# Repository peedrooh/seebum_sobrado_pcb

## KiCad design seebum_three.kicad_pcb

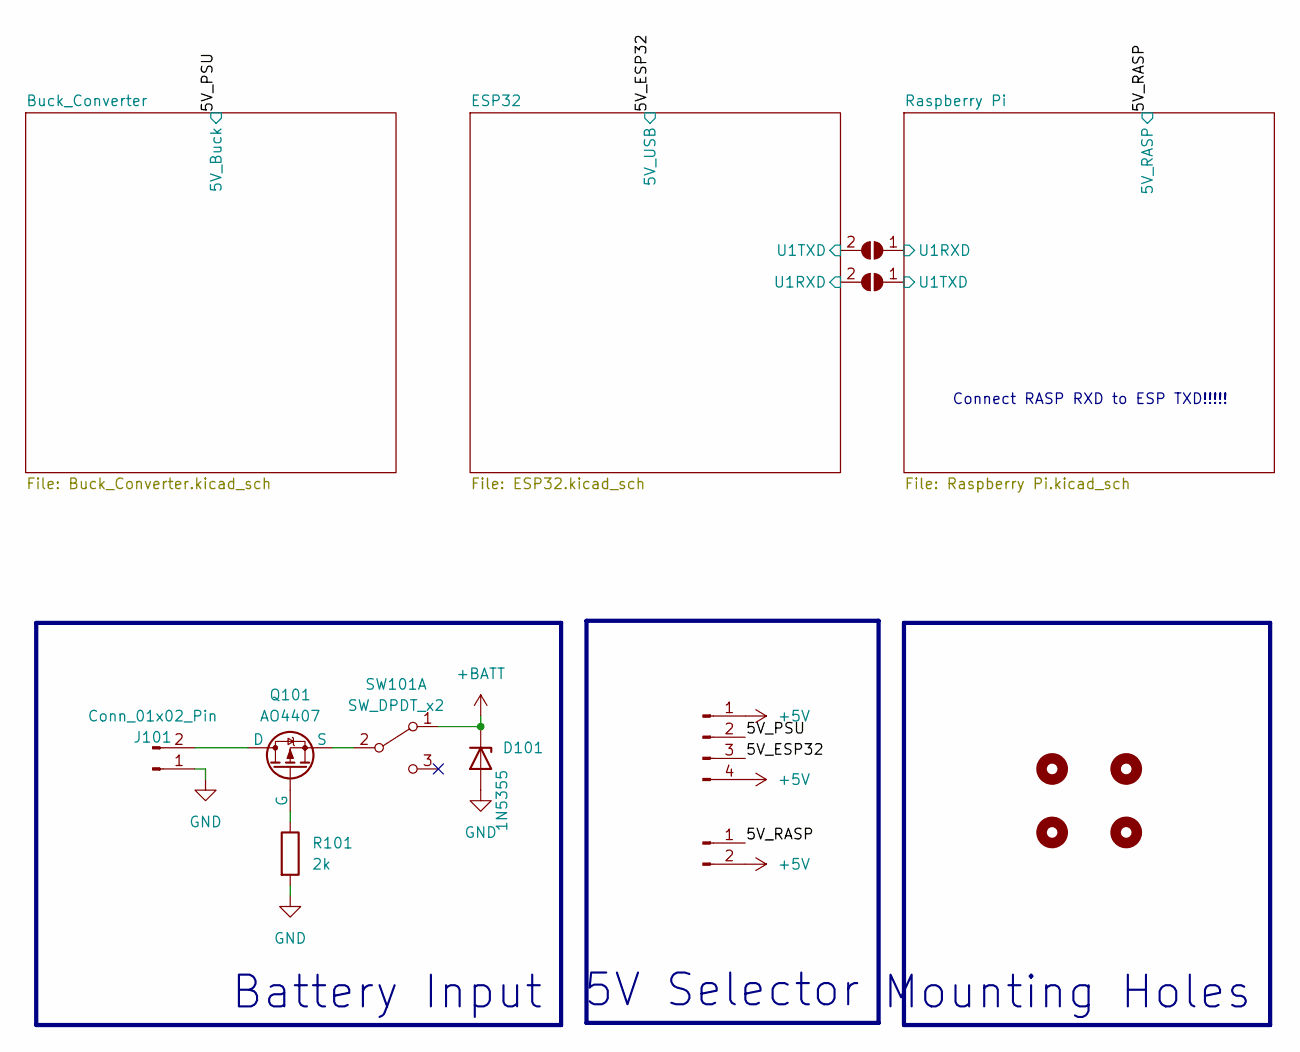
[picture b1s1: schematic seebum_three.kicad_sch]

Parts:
D101: 1N5355; D_DO-201_P3.81mm_Vertical_AnodeUp
H101, H102, H103, H104: MountingHole; M2.5M3
J101: Conn_01x02_Pin; AMASS_XT30UPB-M_1x02_P5.0mm_Vertical
J102: Conn_01x04_Pin; PinHeader_2x02_P2.54mm_Vertical
J103: Conn_01x02_Pin; PinHeader_1x02_P2.54mm_Vertical
JP103, JP104: SolderJumper_2_Open; SolderJumper-2_P1.3mm_Bridged_RoundedPad1.0x1.5mm
Q101: AO4407; SOP-8_3.76x4.96mm_P1.27mm; LCSC C469397
R101: 2k; R_0805_2012Metric; LCSC C17604
SW101: SW_DPDT_x2; 5Amp_Switch; LCSC C2884744

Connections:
+5V: J102.1, J102.4, J103.2; also elsewhere on the board
+BATT: D101.1 (K), SW101.1 (A); also elsewhere on the board
/5V_ESP32: J102.3; also elsewhere on the board
/5V_PSU: J102.2; also elsewhere on the board
/5V_RASP: J103.1; also elsewhere on the board
/ESP32/GPIO17: JP104.2 (B); also elsewhere on the board
/ESP32/GPIO18: JP103.2 (B); also elsewhere on the board
/Raspberry Pi/RASP_RX: JP103.1 (A); also elsewhere on the board
/Raspberry Pi/RASP_TX: JP104.1 (A); also elsewhere on the board
GND: D101.2 (A), J101.1, R101.2; also elsewhere on the board
unnamed: J101.2, Q101.1 (D)
unnamed: Q101.2 (G), R101.1
unnamed: Q101.3 (S), SW101.2 (B)

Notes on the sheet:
Battery Input
Connect RASP RXD to ESP TXD!!!!!
5V Selector
Mounting Holes

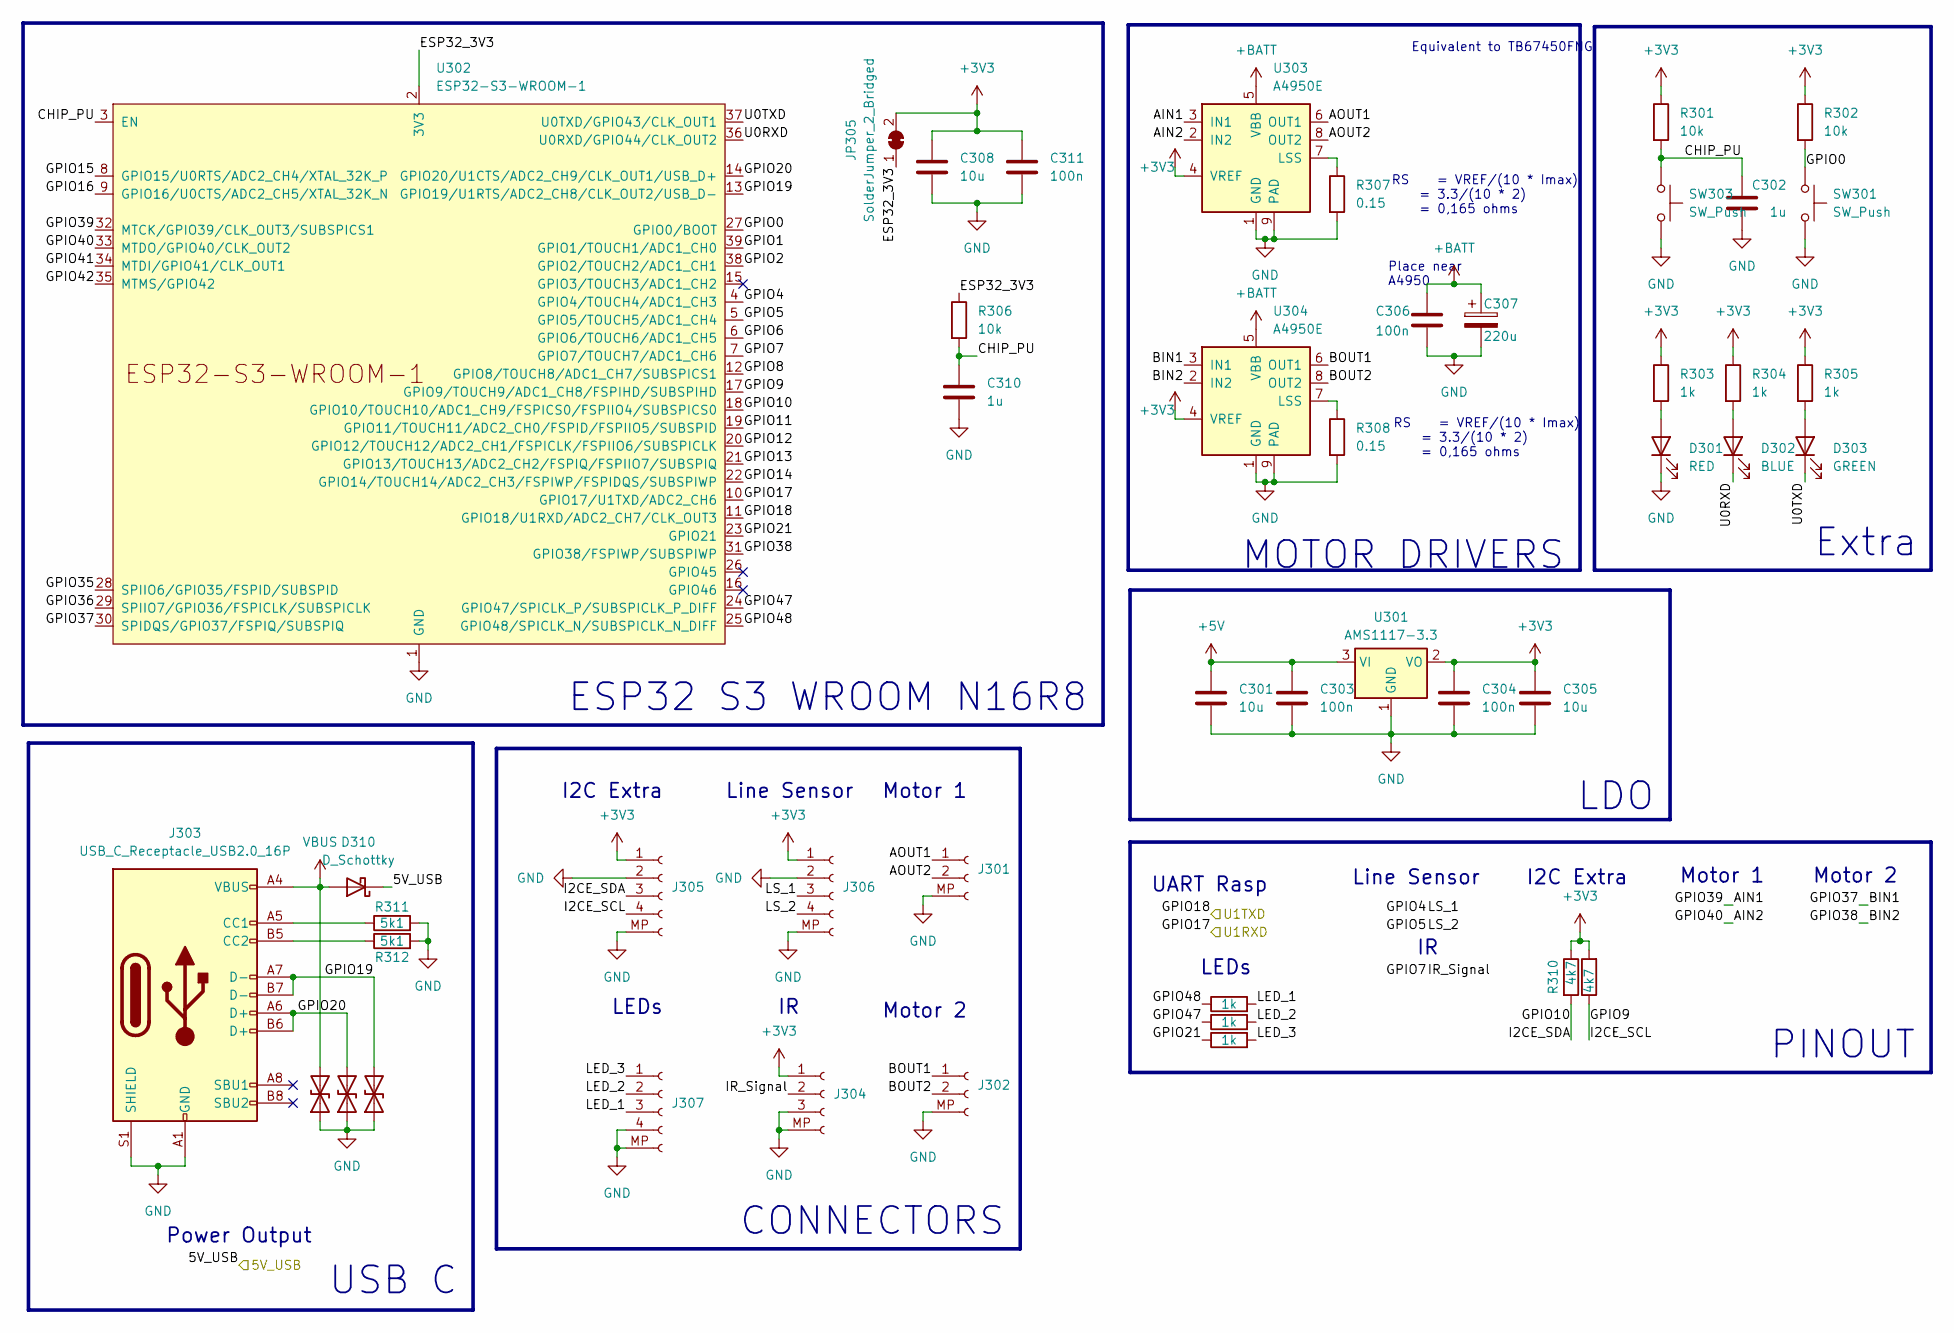
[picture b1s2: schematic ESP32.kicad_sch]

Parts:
C301, C305, C308: 10u; C_0805_2012Metric_Pad1.18x1.45mm_HandSolder
C302, C310: 1u; C_0805_2012Metric_Pad1.18x1.45mm_HandSolder
C303, C304, C306, C311: 100n; C_0805_2012Metric_Pad1.18x1.45mm_HandSolder
C307: 220u; CP_Radial_D10.0mm_P5.00mm
D301: RED; LED_0805_2012Metric
D302: BLUE; LED_0805_2012Metric; LCSC C205441
D303: GREEN; LED_0805_2012Metric; LCSC C84260
D308, D309, D311: D_TVS; D_SOD-523; LCSC C383211
D310: D_Schottky; D_SOD-323; LCSC C2891705
J301, J302: Conn_01x02_Socket; JST_PH_B2B-PH-SM4-TB_1x02-1MP_P2.00mm_Vertical; LCSC C160352
J303: USB_C_Receptacle_USB2.0_16P; USB_C_Receptacle_G-Switch_GT-USB-7010ASV; LCSC C2765186
J304: Conn_01x03_Socket; JST_PH_B3B-PH-SM4-TB_1x03-1MP_P2.00mm_Vertical; LCSC C160353
J305, J306, J307: Conn_01x04_Socket; JST_PH_B4B-PH-SM4-TB_1x04-1MP_P2.00mm_Vertical
JP305: SolderJumper_2_Bridged; SolderJumper-2_P1.3mm_Bridged_RoundedPad1.0x1.5mm
R301, R302, R306: 10k; R_0805_2012Metric_Pad1.20x1.40mm_HandSolder
R303, R304, R305, R313, R314, R315: 1k; R_0805_2012Metric_Pad1.20x1.40mm_HandSolder
R307, R308: 0.15; R_2512_6332Metric_Pad1.40x3.35mm_HandSolder
R309, R310: 4k7; R_0805_2012Metric; LCSC C17673
R311, R312: 5k1; R_0603_1608Metric_Pad0.98x0.95mm_HandSolder
SW301, SW303: SW_Push; SW_SPST_B3U-1000P
U301: AMS1117-3.3; SOT-223-3_TabPin2; LCSC C347222
U302: ESP32-S3-WROOM-1; LCSC C2913205
U303, U304: A4950E; SOIC-8-1EP_3.9x4.9mm_P1.27mm_EP2.41x3.3mm

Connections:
+3V3: C304.1, C305.1, C308.1, C311.1, J304.1, J305.1, J306.1, JP305.2 (B), R301.1, R302.1, R303.1, R304.1, R305.1, R309.2, R310.1, U301.2 (VO), U303.4 (VREF), U304.4 (VREF)
+5V: C301.1, C303.1, U301.3 (VI); also elsewhere on the board
+BATT: C306.1, C307.1, U303.5 (VBB), U304.5 (VBB); also elsewhere on the board
/5V_ESP32: D310.1 (K); also elsewhere on the board
/ESP32/AIN1: U302.32 (MTCK/GPIO39/CLK_OUT3/SUBSPICS1), U303.3 (IN1)
/ESP32/AIN2: U302.33 (MTDO/GPIO40/CLK_OUT2), U303.2 (IN2)
/ESP32/AOUT1: J301.1, U303.6 (OUT1)
/ESP32/AOUT2: J301.2, U303.8 (OUT2)
/ESP32/BIN1: U302.30 (SPIDQS/GPIO37/FSPIQ/SUBSPIQ), U304.3 (IN1)
/ESP32/BIN2: U302.31 (GPIO38/FSPIWP/SUBSPIWP), U304.2 (IN2)
/ESP32/BOUT1: J302.1, U304.6 (OUT1)
/ESP32/BOUT2: J302.2, U304.8 (OUT2)
/ESP32/CHIP_PU: C302.1, C310.1, R301.2, R306.2, SW303.1, U302.3 (EN)
/ESP32/ESP32_3V3: JP305.1 (A), R306.1, U302.2 (3V3)
/ESP32/GPIO0: R302.2, SW301.1, U302.27 (GPIO0/BOOT)
/ESP32/GPIO1: U302.39 (GPIO1/TOUCH1/ADC1_CH0)
/ESP32/GPIO2: U302.38 (GPIO2/TOUCH2/ADC1_CH1)
/ESP32/GPIO4: J306.3, U302.4 (GPIO4/TOUCH4/ADC1_CH3)
/ESP32/GPIO5: J306.4, U302.5 (GPIO5/TOUCH5/ADC1_CH4)
/ESP32/GPIO6: U302.6 (GPIO6/TOUCH6/ADC1_CH5)
/ESP32/GPIO7: J304.2, U302.7 (GPIO7/TOUCH7/ADC1_CH6)
/ESP32/GPIO8: U302.12 (GPIO8/TOUCH8/ADC1_CH7/SUBSPICS1)
/ESP32/GPIO9: J305.4, R309.1, U302.17 (GPIO9/TOUCH9/ADC1_CH8/FSPIHD/SUBSPIHD)
/ESP32/GPIO10: J305.3, R310.2, U302.18 (GPIO10/TOUCH10/ADC1_CH9/FSPICS0/FSPIIO4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)
/ESP32/GPIO11: U302.19 (GPIO11/TOUCH11/ADC2_CH0/FSPID/FSPIIO5/S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)
/ESP32/GPIO12: U302.20 (GPIO12/TOUCH12/ADC2_CH1/FSPICLK/FSPIIO6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)
/ESP32/GPIO13: U302.21 (GPIO13/TOUCH13/ADC2_CH2/FSPIQ/FSPIIO7/S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)
/ESP32/GPIO14: U302.22 (GPIO14/TOUCH14/ADC2_CH3/FSPIWP/FSPIDQS/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)
/ESP32/GPIO15: U302.8 (GPIO15/U0RTS/ADC2_CH4/XTAL_32K_P)
/ESP32/GPIO16: U302.9 (GPIO16/U0CTS/ADC2_CH5/XTAL_32K_N)
/ESP32/GPIO17: U302.10 (GPIO17/U1TXD/ADC2_CH6); also elsewhere on the board
/ESP32/GPIO18: U302.11 (GPIO18/U1RXD/ADC2_CH7/CLK_OUT3); also elsewhere on the board
/ESP32/GPIO19: D311.2 (A2), J303.A7 (D-), J303.B7 (D-), U302.13 (GPIO19/U1RTS/ADC2_CH8/CLK_OUT2/USB_D-)
/ESP32/GPIO20: D309.2 (A2), J303.A6 (D+), J303.B6 (D+), U302.14 (GPIO20/U1CTS/ADC2_CH9/CLK_OUT1/USB_D+)
/ESP32/GPIO21: R315.1, U302.23 (GPIO21)
/ESP32/GPIO35: U302.28 (SPIIO6/GPIO35/FSPID/SUBSPID)
/ESP32/GPIO36: U302.29 (SPIIO7/GPIO36/FSPICLK/SUBSPICLK)
/ESP32/GPIO41: U302.34 (MTDI/GPIO41/CLK_OUT1)
/ESP32/GPIO42: U302.35 (MTMS/GPIO42)
/ESP32/GPIO47: R314.1, U302.24 (GPIO47/SPICLK_P/SUBSPICLK_P_DIFF)
/ESP32/GPIO48: R313.1, U302.25 (GPIO48/SPICLK_N/SUBSPICLK_N_DIFF)
/ESP32/LED_1: J307.3, R313.2
/ESP32/LED_2: J307.2, R314.2
/ESP32/LED_3: J307.1, R315.2
/ESP32/U0RXD: D302.1 (K), U302.36 (U0RXD/GPIO44/CLK_OUT2)
/ESP32/U0TXD: D303.1 (K), U302.37 (U0TXD/GPIO43/CLK_OUT1)
GND: C301.2, C302.2, C303.2, C304.2, C305.2, C306.2, C307.2, C308.2, C310.2, C311.2, D301.1 (K), D308.1 (A1), D309.1 (A1), D311.1 (A1), J301.MP (Pin_3), J302.MP (Pin_3), J303.A1 (GND), J303.A12 (GND), J303.B1 (GND), J303.B12 (GND), J303.S1 (SHIELD), J304.3, J304.MP (Pin_4), J305.2, J305.MP (Pin_5), J306.2, J306.MP (Pin_5), J307.4, J307.MP (Pin_5), R307.2, R308.2, R311.2, R312.2, SW301.2, SW303.2, U301.1 (GND), U302.1 (GND), U302.40 (GND), U302.41 (GND), U303.1 (GND), U303.9 (PAD), U304.1 (GND), U304.9 (PAD); also elsewhere on the board
unnamed: D301.2 (A), R303.2
unnamed: D302.2 (A), R304.2
unnamed: D303.2 (A), R305.2
unnamed: J303.A5 (CC1), R311.1
unnamed: J303.B5 (CC2), R312.1
unnamed: R307.1, U303.7 (LSS)
unnamed: R308.1, U304.7 (LSS)
VBUS: D308.2 (A2), D310.2 (A), J303.A4 (VBUS), J303.A9 (VBUS), J303.B4 (VBUS), J303.B9 (VBUS)

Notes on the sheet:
PINOUT
RS = VREF/(10 * Imax) = 3.3/(10 * 2) = 0,165 ohms
USB C
Place near A4950
ESP32 S3 WROOM N16R8
Motor 2
Line Sensor
LEDs
I2C Extra
Motor 1
Power Output
MOTOR DRIVERS
CONNECTORS
Equivalent to TB67450FNG
Extra
LDO
UART Rasp

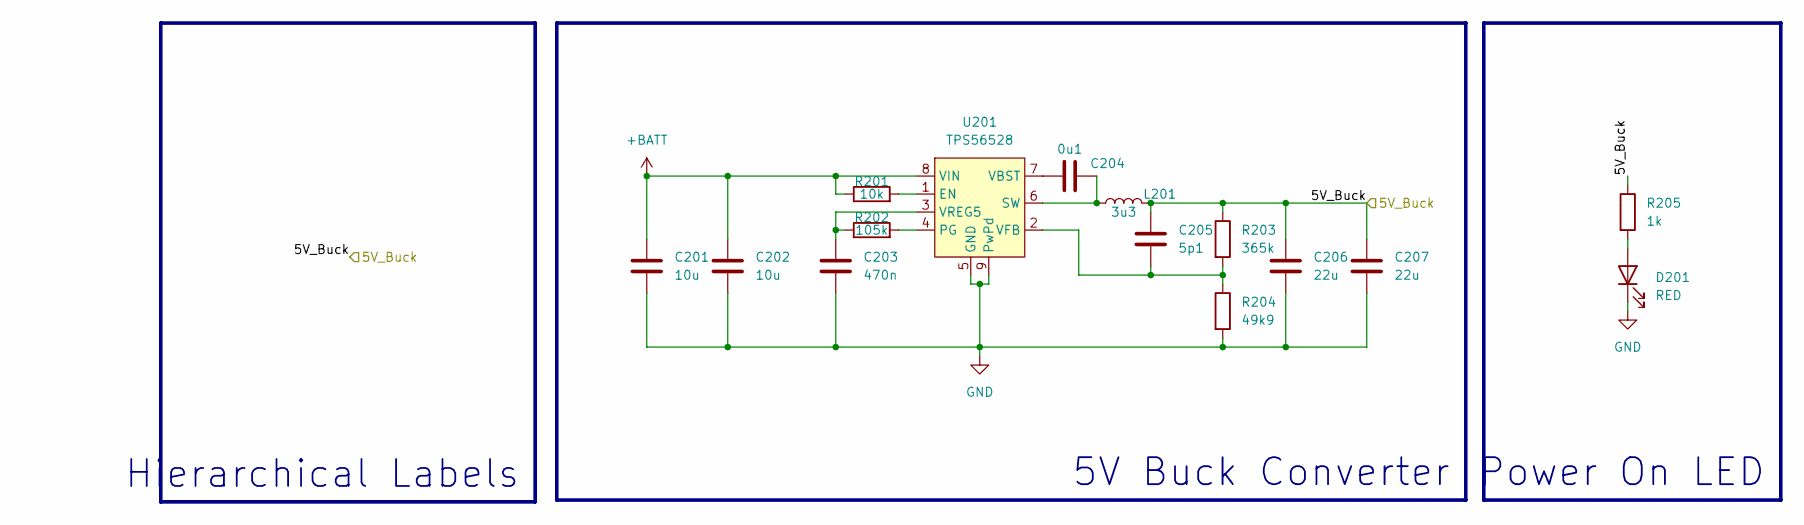
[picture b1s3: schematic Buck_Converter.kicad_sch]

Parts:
C201: 10u; C_1210_3225Metric_Pad1.33x2.70mm_HandSolder; LCSC C2918502
C202: 10u; C_1210_3225Metric_Pad1.33x2.70mm_HandSolder
C203: 470n; C_0805_2012Metric_Pad1.18x1.45mm_HandSolder
C204: 0u1; C_0805_2012Metric_Pad1.18x1.45mm_HandSolder
C205: 5p1; C_0805_2012Metric_Pad1.18x1.45mm_HandSolder
C206, C207: 22u; C_0805_2012Metric_Pad1.18x1.45mm_HandSolder
D201: RED; LED_0805_2012Metric
L201: 3u3; L_Bourns_SRP1050WA; LCSC C497894
R201: 10k; R_0805_2012Metric_Pad1.20x1.40mm_HandSolder
R202: 105k; R_0805_2012Metric_Pad1.20x1.40mm_HandSolder; LCSC C3000727
R203: 365k; R_0805_2012Metric_Pad1.20x1.40mm_HandSolder; LCSC C2999471
R204: 49k9; R_0805_2012Metric_Pad1.20x1.40mm_HandSolder; LCSC C17719
R205: 1k; R_0805_2012Metric_Pad1.20x1.40mm_HandSolder
U201: TPS56528; Texas_HSOP-8-1EP_3.9x4.9mm_P1.27mm_ThermalVias; LCSC C138716

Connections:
+BATT: C201.1, C202.1, R201.1, U201.8 (VIN); also elsewhere on the board
/5V_PSU: C205.1, C206.1, C207.1, L201.2, R203.1, R205.1; also elsewhere on the board
GND: C201.2, C202.2, C203.2, C206.2, C207.2, D201.1 (K), R204.2, U201.5 (GND), U201.9 (PwPd); also elsewhere on the board
unnamed: D201.2 (A), R205.2
unnamed: R201.2, U201.1 (EN)
unnamed: R202.2, U201.4 (PG)
unnamed: C204.2, L201.1, U201.6 (SW)
unnamed: C204.1, U201.7 (VBST)
unnamed: C205.2, R203.2, R204.1, U201.2 (VFB)
unnamed: C203.1, R202.1, U201.3 (VREG5)

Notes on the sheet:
Power On LED
Hierarchical Labels
5V Buck Converter

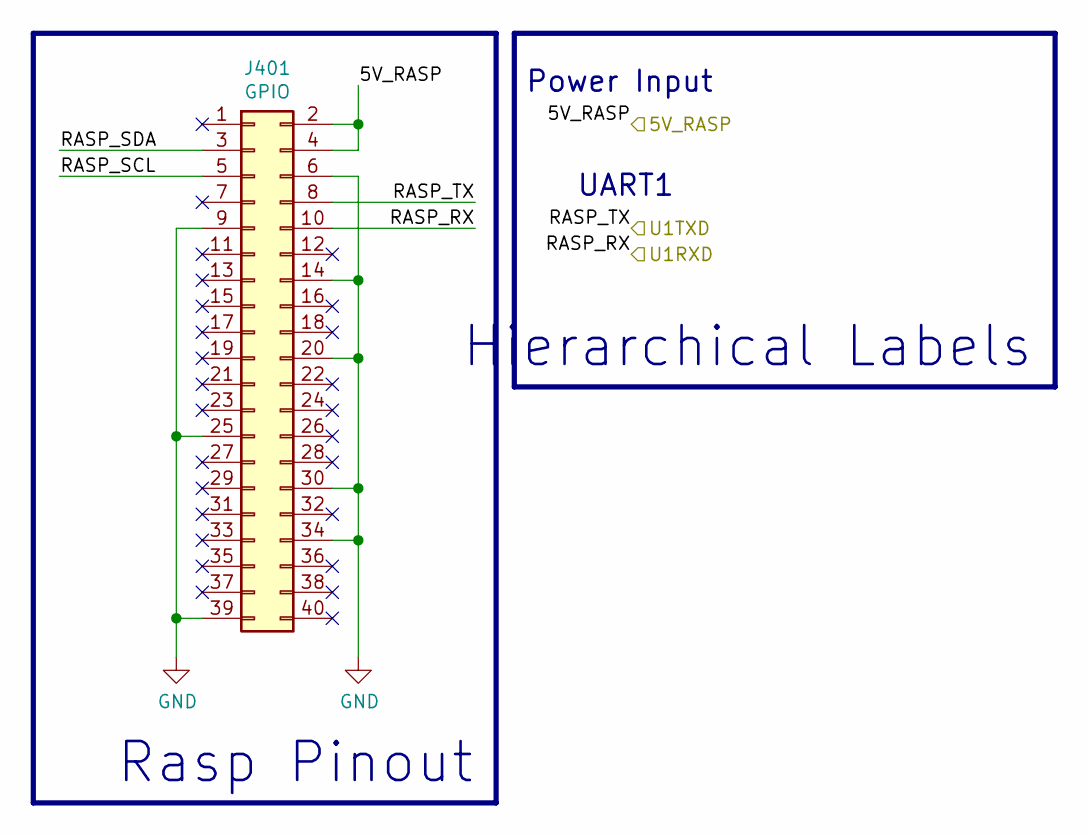
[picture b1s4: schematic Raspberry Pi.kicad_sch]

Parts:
J401: GPIO; PinSocket_2x20_P2.54mm_Vertical

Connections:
/5V_RASP: J401.2, J401.4; also elsewhere on the board
/Raspberry Pi/RASP_RX: J401.10; also elsewhere on the board
/Raspberry Pi/RASP_SCL: J401.5
/Raspberry Pi/RASP_SDA: J401.3
/Raspberry Pi/RASP_TX: J401.8; also elsewhere on the board
GND: J401.6, J401.9, J401.14, J401.20, J401.25, J401.30, J401.34, J401.39; also elsewhere on the board

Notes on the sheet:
Power Input
Rasp Pinout
Hierarchical Labels
UART1

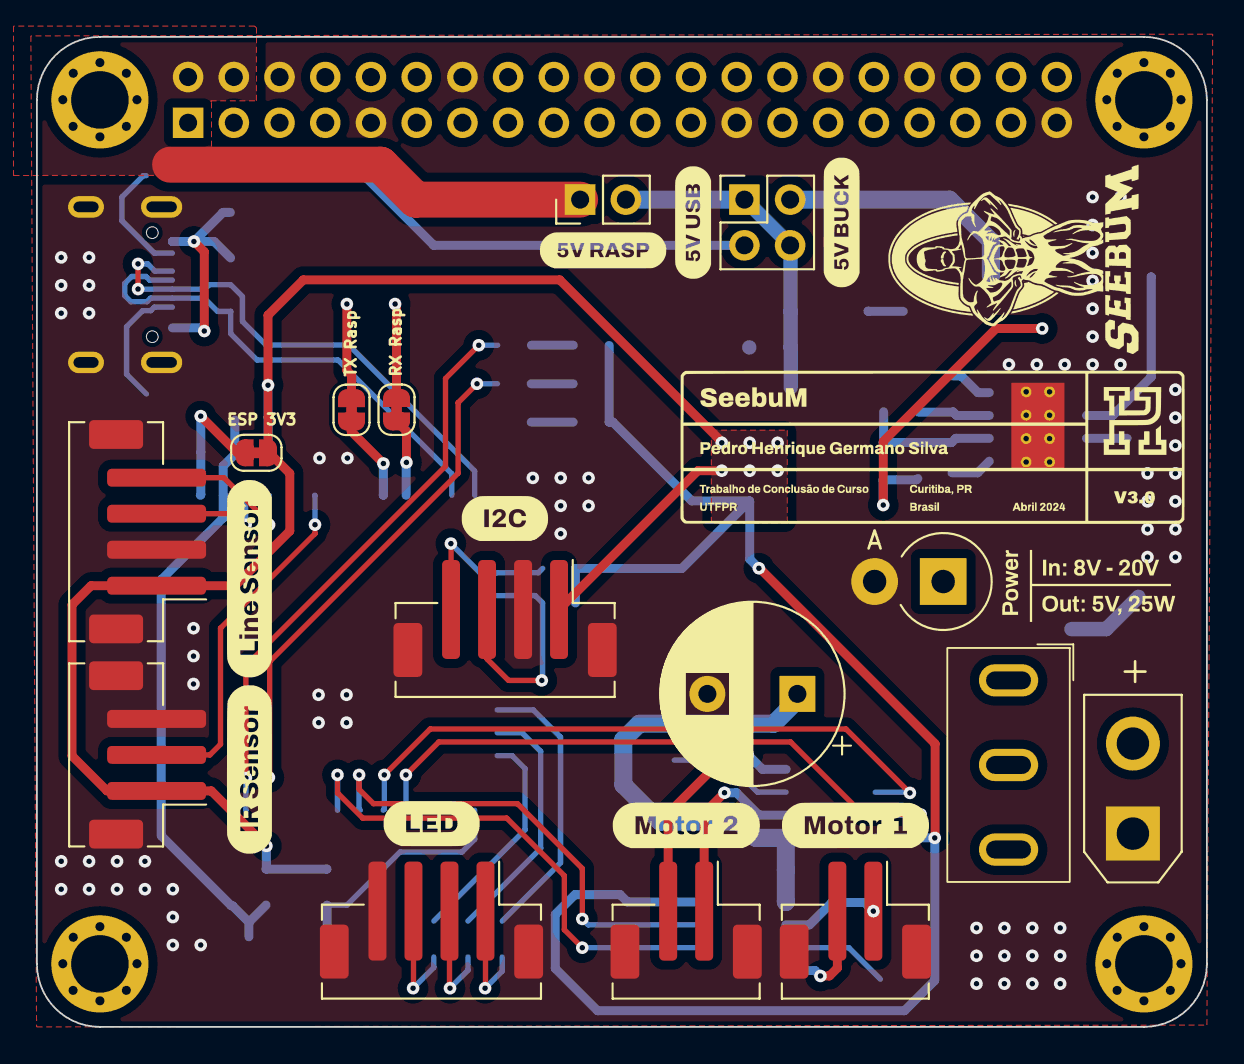
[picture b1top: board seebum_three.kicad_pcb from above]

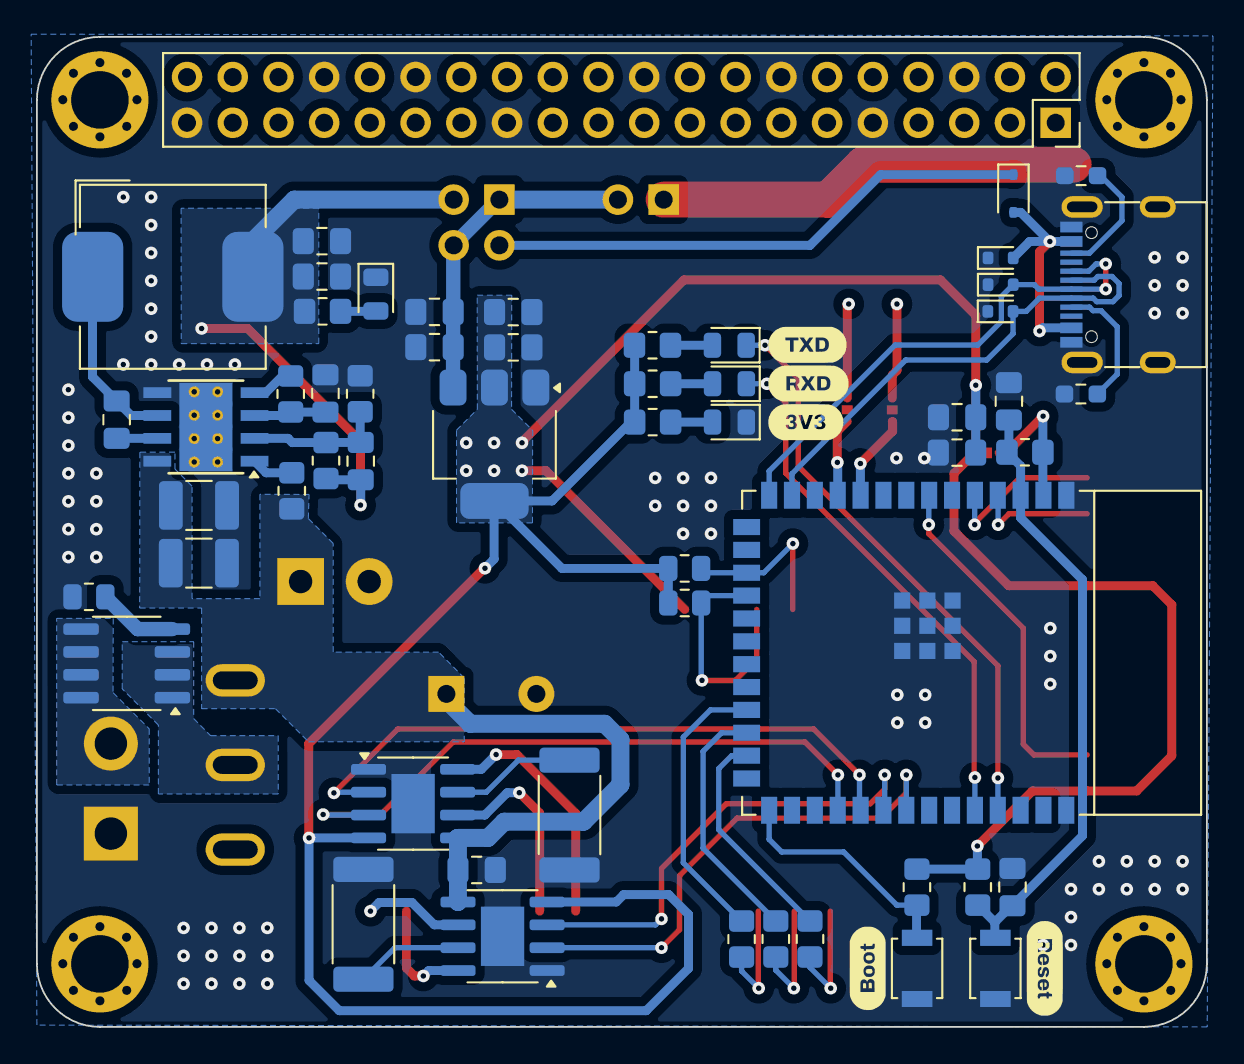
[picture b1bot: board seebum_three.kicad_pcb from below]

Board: 4 copper layers, 65.0 x 55.0 mm, 75 parts (56 on the bottom side), 55 nets.

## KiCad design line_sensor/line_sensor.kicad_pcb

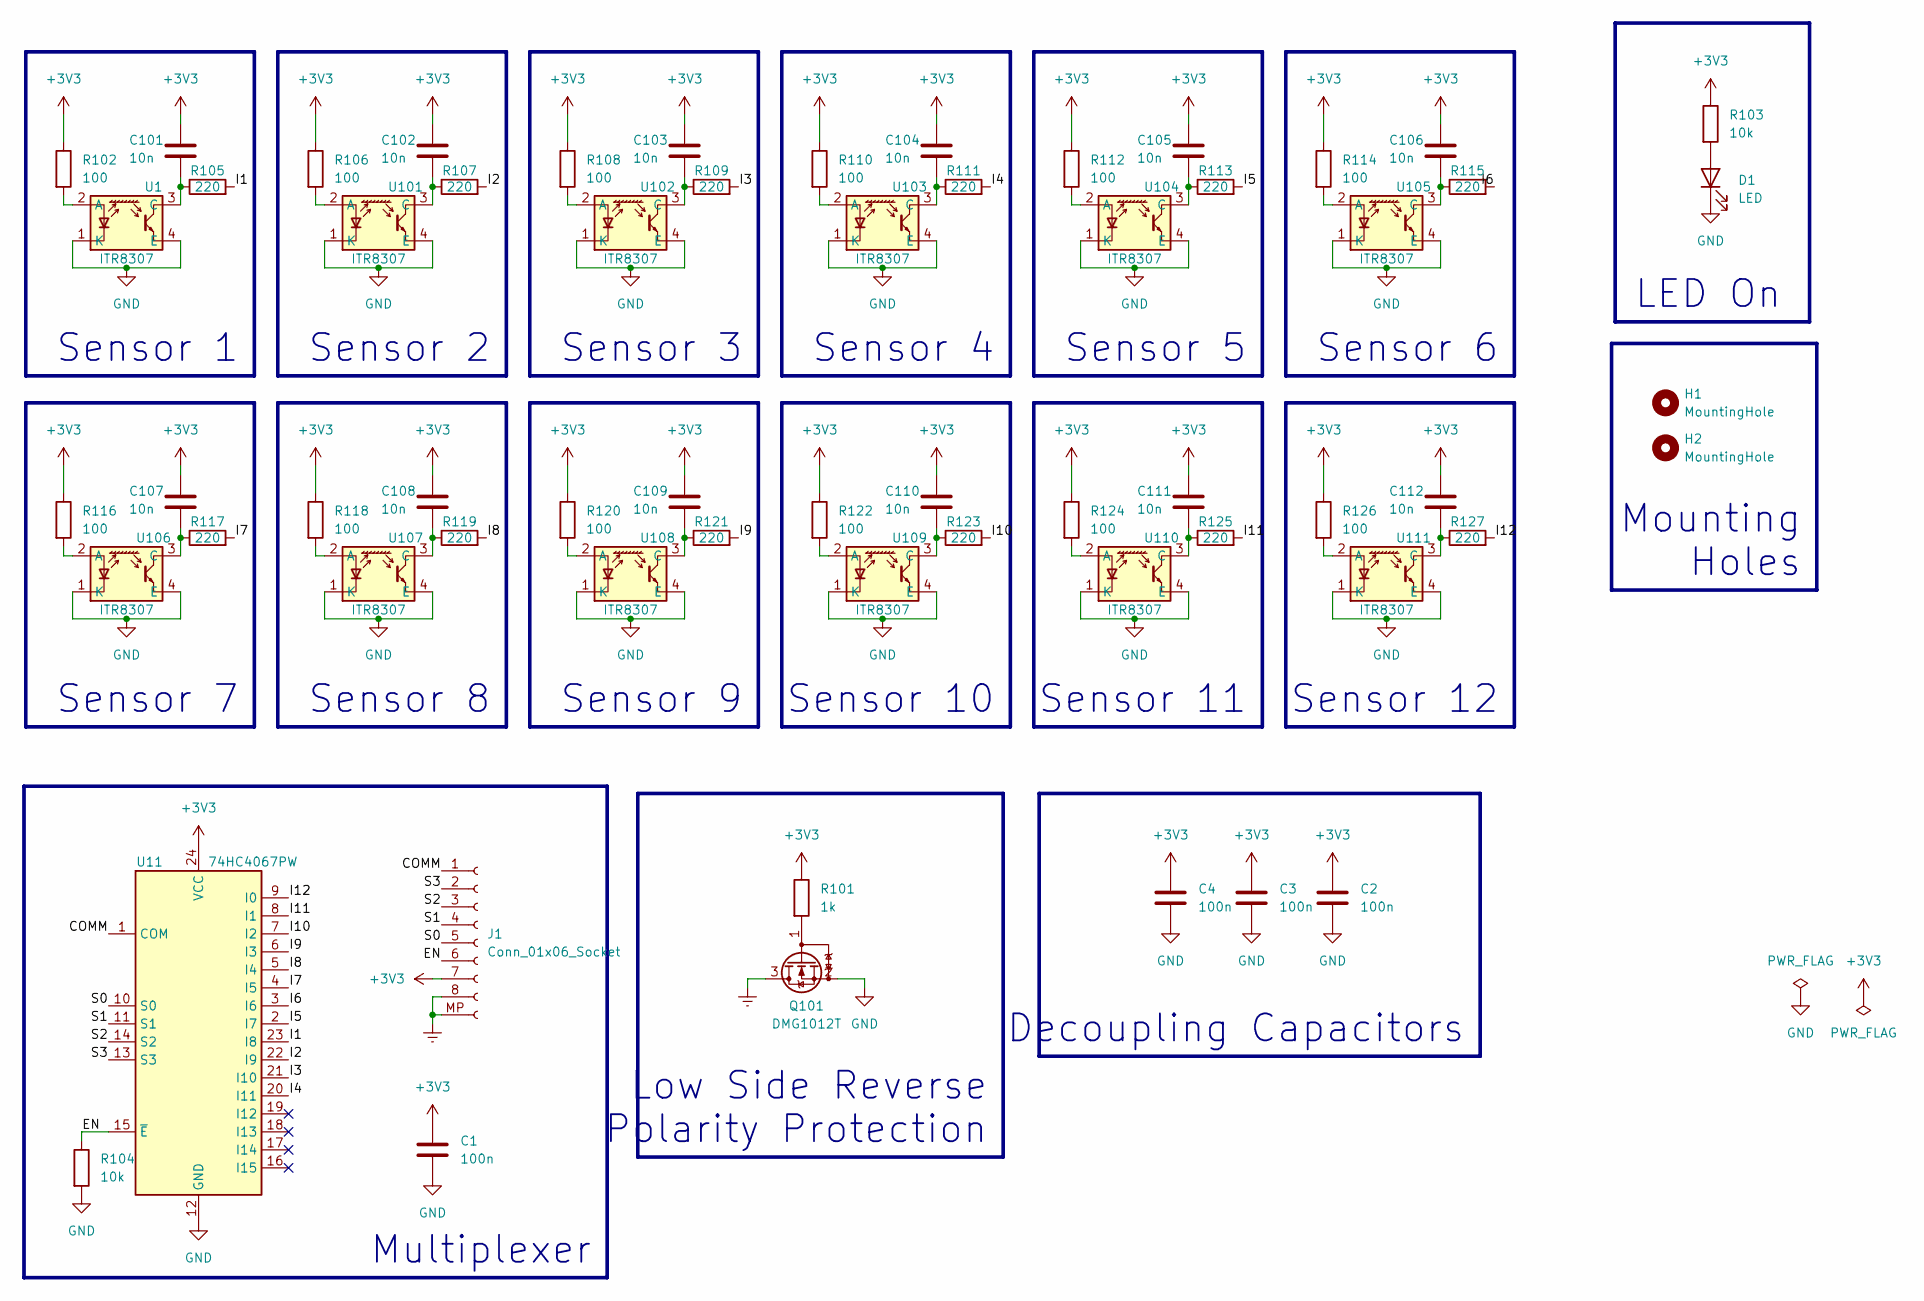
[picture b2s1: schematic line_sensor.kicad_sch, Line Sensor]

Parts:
C1, C2, C3, C4: 100n; C_0805_2012Metric_Pad1.18x1.45mm_HandSolder; LCSC C38141
C101, C102, C103, C104, C105, C106, C107, C108, C109, C110, C111, C112: 10n; C_0805_2012Metric_Pad1.18x1.45mm_HandSolder
D1: LED; LED_0805_2012Metric; LCSC C391863
H1, H2: MountingHole; MountingHole_3.2mm_M3_Pad_Via
J1: Conn_01x06_Socket; JST_PH_B8B-PH-SM4-TB_1x08-1MP_P2.00mm_Vertical
Q101: DMG1012T; SOT-523; LCSC C20512
R101: 1k; R_0805_2012Metric; LCSC C17513
R102, R106, R108, R110, R112, R114, R116, R118, R120, R122, R124, R126: 100; R_0805_2012Metric
R103, R104: 10k; R_0805_2012Metric
R105, R107, R109, R111, R113, R115, R117, R119, R121, R123, R125, R127: 220; R_0805_2012Metric
U1, U101, U102, U103, U104, U105, U106, U107, U108, U109, U110, U111: ITR8307; ITR8307_S18_TR8_B; LCSC C115037
U11: 74HC4067PW; TSSOP-24_4.4x7.8mm_P0.65mm; LCSC C179326

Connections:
+3V3: C1.1, C2.1, C3.1, C4.1, C101.1, C102.1, C103.1, C104.1, C105.1, C106.1, C107.1, C108.1, C109.1, C110.1, C111.1, C112.1, J1.7, R101.1, R102.1, R103.1, R106.1, R108.1, R110.1, R112.1, R114.1, R116.1, R118.1, R120.1, R122.1, R124.1, R126.1, U11.24 (VCC)
/COMM: J1.1, U11.1 (COM)
/EN: J1.6, R104.1, U11.15 (~E)
/I1: R105.2, U11.23 (I8)
/I2: R107.2, U11.22 (I9)
/I3: R109.2, U11.21 (I10)
/I4: R111.2, U11.20 (I11)
/I5: R113.2, U11.2 (I7)
/I6: R115.2, U11.3 (I6)
/I7: R117.2, U11.4 (I5)
/I8: R119.2, U11.5 (I4)
/I9: R121.2, U11.6 (I3)
/I10: R123.2, U11.7 (I2)
/I11: R125.2, U11.8 (I1)
/I12: R127.2, U11.9 (I0)
/S0: J1.5, U11.10 (S0)
/S1: J1.4, U11.11 (S1)
/S2: J1.3, U11.14 (S2)
/S3: J1.2, U11.13 (S3)
Earth: J1.8, J1.MP (Pin_9), Q101.3 (D)
GND: C1.2, C2.2, C3.2, C4.2, D1.1 (K), Q101.2 (S), R104.2, U1.1 (K), U1.4 (E), U11.12 (GND), U101.1 (K), U101.4 (E), U102.1 (K), U102.4 (E), U103.1 (K), U103.4 (E), U104.1 (K), U104.4 (E), U105.1 (K), U105.4 (E), U106.1 (K), U106.4 (E), U107.1 (K), U107.4 (E), U108.1 (K), U108.4 (E), U109.1 (K), U109.4 (E), U110.1 (K), U110.4 (E), U111.1 (K), U111.4 (E)
unnamed: D1.2 (A), R103.2
unnamed: Q101.1 (G), R101.2
unnamed: R102.2, U1.2 (A)
unnamed: C101.2, R105.1, U1.3 (C)
unnamed: R106.2, U101.2 (A)
unnamed: C102.2, R107.1, U101.3 (C)
unnamed: R108.2, U102.2 (A)
unnamed: C103.2, R109.1, U102.3 (C)
unnamed: R110.2, U103.2 (A)
unnamed: C104.2, R111.1, U103.3 (C)
unnamed: R112.2, U104.2 (A)
unnamed: C105.2, R113.1, U104.3 (C)
unnamed: R114.2, U105.2 (A)
unnamed: C106.2, R115.1, U105.3 (C)
unnamed: R116.2, U106.2 (A)
unnamed: C107.2, R117.1, U106.3 (C)
unnamed: R118.2, U107.2 (A)
unnamed: C108.2, R119.1, U107.3 (C)
unnamed: R120.2, U108.2 (A)
unnamed: C109.2, R121.1, U108.3 (C)
unnamed: R122.2, U109.2 (A)
unnamed: C110.2, R123.1, U109.3 (C)
unnamed: R124.2, U110.2 (A)
unnamed: C111.2, R125.1, U110.3 (C)
unnamed: R126.2, U111.2 (A)
unnamed: C112.2, R127.1, U111.3 (C)

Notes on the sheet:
Low Side Reverse Polarity Protection
Sensor 4
Sensor 3
Sensor 12
Sensor 2
Sensor 8
Sensor 1
Sensor 10
Sensor 5
LED On
Sensor 9
Sensor 11
Sensor 6
Mounting Holes
Decoupling Capacitors
Multiplexer
Sensor 7

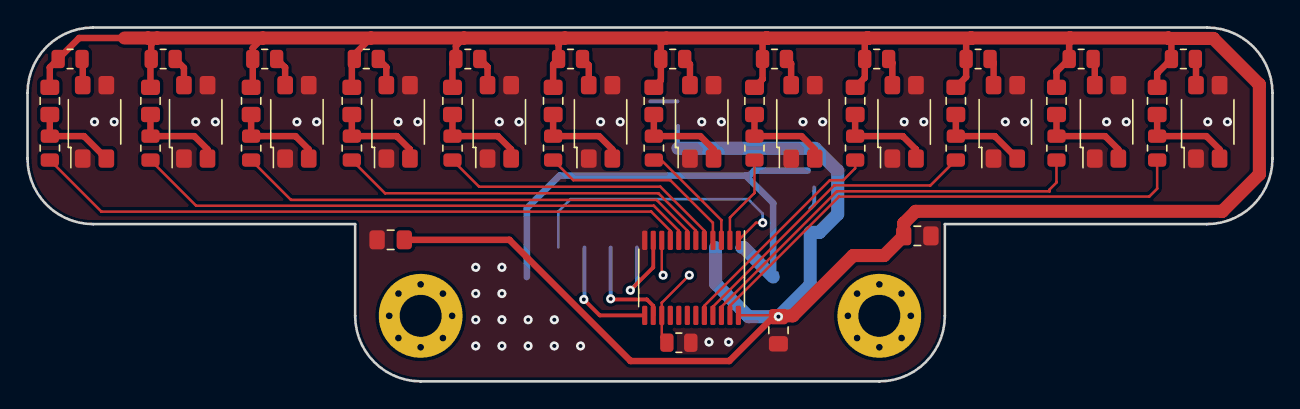
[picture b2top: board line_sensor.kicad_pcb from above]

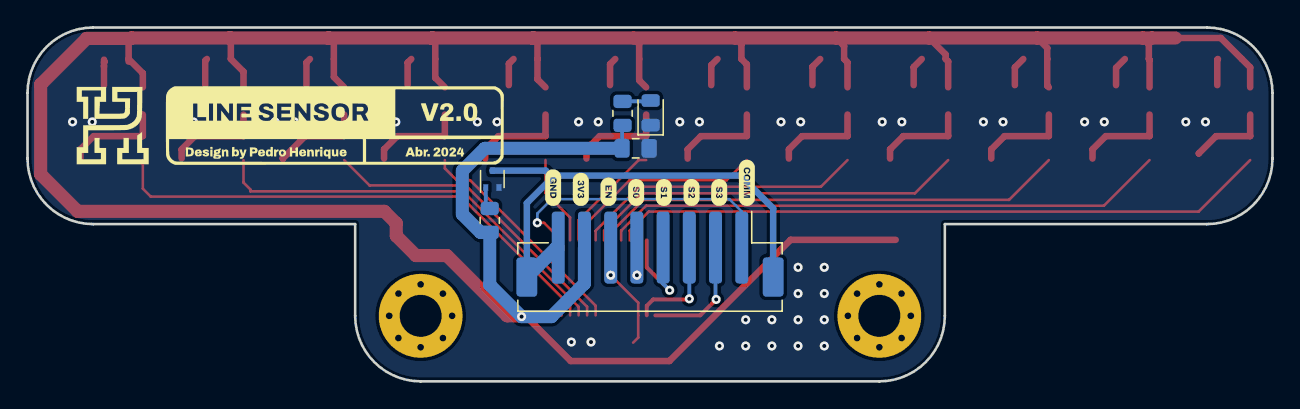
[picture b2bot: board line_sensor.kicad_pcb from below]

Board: 2 copper layers, 95.0 x 27.0 mm, 61 parts (6 on the bottom side), 47 nets.

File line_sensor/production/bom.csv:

Designator,Footprint,Quantity,Value,LCSC Part #
"C1, C2, C3, C4",0805,4,100n,C38141
"C101, C102, C103, C104, C105, C106, C107, C108, C109, C110, C111, C112",0805,12,10n,
D1,0805,1,LED,C391863
"H1, H2",MountingHole_3.2mm_M3_Pad_Via,2,MountingHole,
J1,JST_PH_B8B-PH-SM4-TB_1x08-1MP_P2.00mm_Vertical,1,Conn_01x06_Socket,
Q101,SOT-523,1,DMG1012T,C20512
R101,0805,1,1k,C17513
"R102, R106, R108, R110, R112, R114, R116, R118, R120, R122, R124, R126",0805,12,100,
"R103, R104",0805,2,10k,
"R105, R107, R109, R111, R113, R115, R117, R119, R121, R123, R125, R127",0805,12,220,
"U1, U101, U102, U103, U104, U105, U106, U107, U108, U109, U110, U111",ITR8307_S18_TR8_B,12,ITR8307,C115037
U11,TSSOP-24_4.4x7.8mm_P0.65mm,1,74HC4067PW,C179326
